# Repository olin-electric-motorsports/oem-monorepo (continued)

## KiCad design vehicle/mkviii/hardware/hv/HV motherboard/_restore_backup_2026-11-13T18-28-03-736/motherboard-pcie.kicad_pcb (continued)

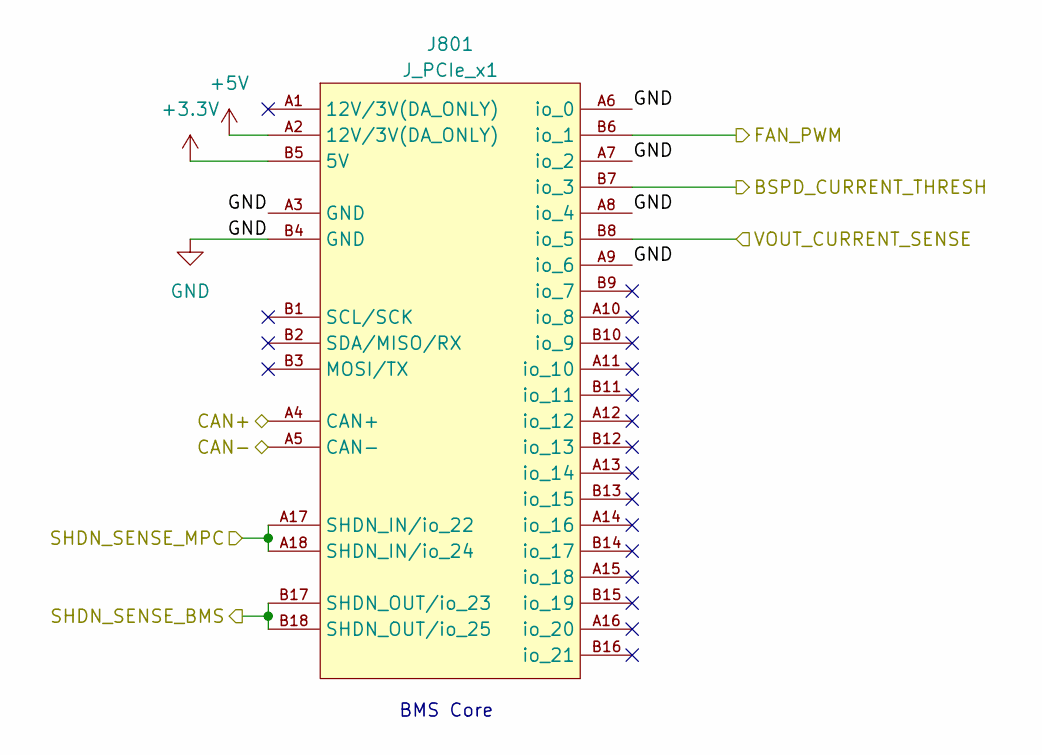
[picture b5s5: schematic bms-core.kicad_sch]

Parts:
J801: J_PCIe_x1; MPN 2-1761465-1

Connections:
+3.3V: J801.B5 (5V); also elsewhere on the board
+5V: J801.A2 (12V/3V(DA_ONLY)); also elsewhere on the board
/BSPD_CURRENT_THRESH: J801.B7 (io_3); also elsewhere on the board
/CAN+: J801.A4 (CAN+); also elsewhere on the board
/CAN-: J801.A5 (CAN-); also elsewhere on the board
/FAN_PWM: J801.B6 (io_1); also elsewhere on the board
/SHDN_SENSE_BMS: J801.B17 (SHDN_OUT/io_23), J801.B18 (SHDN_OUT/io_25); also elsewhere on the board
/SHDN_SENSE_MPC: J801.A17 (SHDN_IN/io_22), J801.A18 (SHDN_IN/io_24); also elsewhere on the board
/VOUT_CURRENT_SENSE: J801.B8 (io_5); also elsewhere on the board

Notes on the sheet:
BMS Core

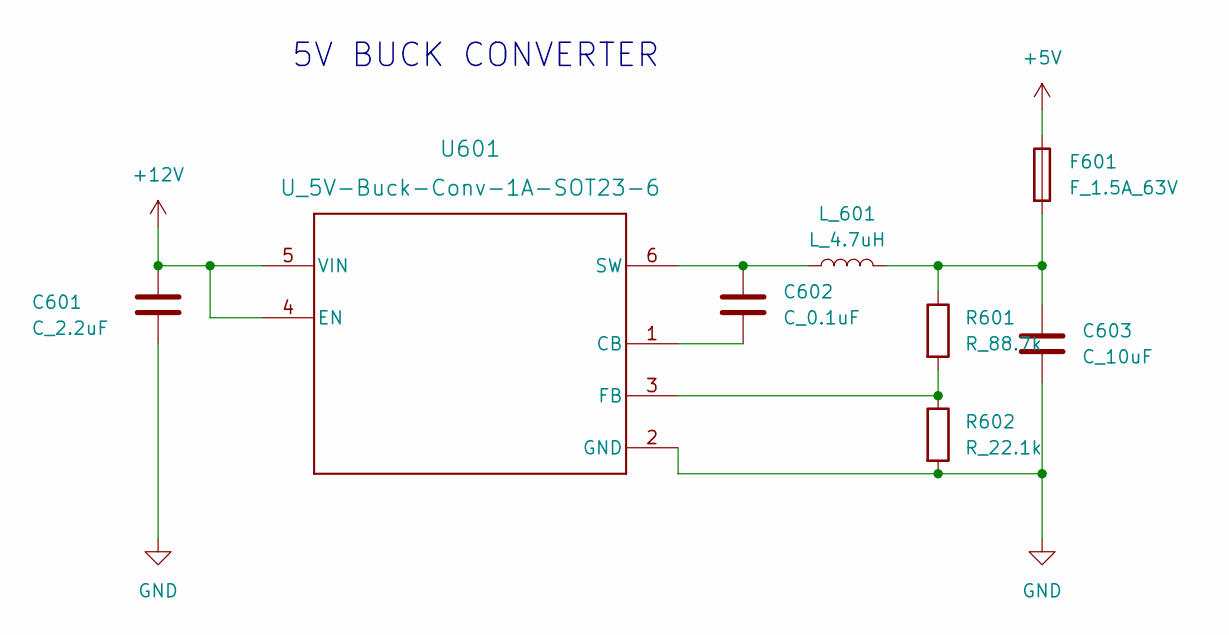
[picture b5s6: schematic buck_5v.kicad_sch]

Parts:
C601: C_2.2uF; C_0603_1608Metric; MPN GRM188R61E225KA12J
C602: C_0.1uF; C_0603_1608Metric; MPN C0603C104Z4VACTU
C603: C_10uF; C_0603_1608Metric; MPN GRM188D71A106KA73D
F601: F_1.5A_63V; Fuse_1206_3216Metric; MPN 046601.5NR
L_601: L_4.7uH; IND_ASPI-4030S-4R7M-T; MPN ASPI-4030S-4R7M-T
R601: R_88.7k; R_0603_1608Metric; MPN RMCF0603FT75K0
R602: R_22.1k; R_0603_1608Metric; MPN RMCF0603FT23K7
U601: U_5V-Buck-Conv-1A-SOT23-6; DBV0006A-IPC_A

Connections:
+5V: F601.1; also elsewhere on the board
unnamed: C603.1, F601.2, L_601.2, R601.1
unnamed: C602.2, U601.1 (CB)
unnamed: R601.2, R602.1, U601.3 (FB)
unnamed: C602.1, L_601.1, U601.6 (SW)

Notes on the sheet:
5V BUCK CONVERTER

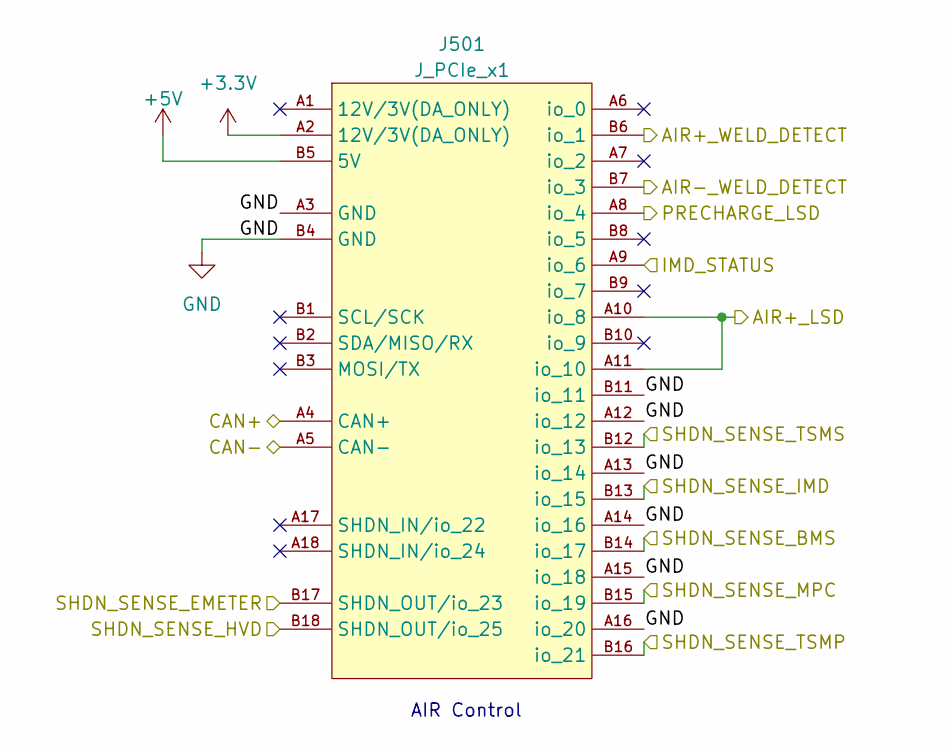
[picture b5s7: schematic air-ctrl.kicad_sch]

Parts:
J501: J_PCIe_x1; MPN 2-1761465-1

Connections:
+3.3V: J501.A2 (12V/3V(DA_ONLY)); also elsewhere on the board
+5V: J501.B5 (5V); also elsewhere on the board
/AIR+_LSD: J501.A10 (io_8), J501.A11 (io_10); also elsewhere on the board
/AIR+_WELD_DETECT: J501.B6 (io_1); also elsewhere on the board
/AIR-_WELD_DETECT: J501.B7 (io_3); also elsewhere on the board
/CAN+: J501.A4 (CAN+); also elsewhere on the board
/CAN-: J501.A5 (CAN-); also elsewhere on the board
/FINAL_SHDN: J501.B12 (io_13); also elsewhere on the board
/IMD_STATUS: J501.A9 (io_6); also elsewhere on the board
/PRECHARGE_LSD: J501.A8 (io_4); also elsewhere on the board
/SHDN_SENSE_BMS: J501.B14 (io_17); also elsewhere on the board
/SHDN_SENSE_EMETER: J501.B17 (SHDN_OUT/io_23); also elsewhere on the board
/SHDN_SENSE_HVD: J501.B18 (SHDN_OUT/io_25); also elsewhere on the board
/SHDN_SENSE_IMD: J501.B13 (io_15); also elsewhere on the board
/SHDN_SENSE_MPC: J501.B15 (io_19); also elsewhere on the board
/SHDN_SENSE_TSMP: J501.B16 (io_21); also elsewhere on the board

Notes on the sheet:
AIR Control

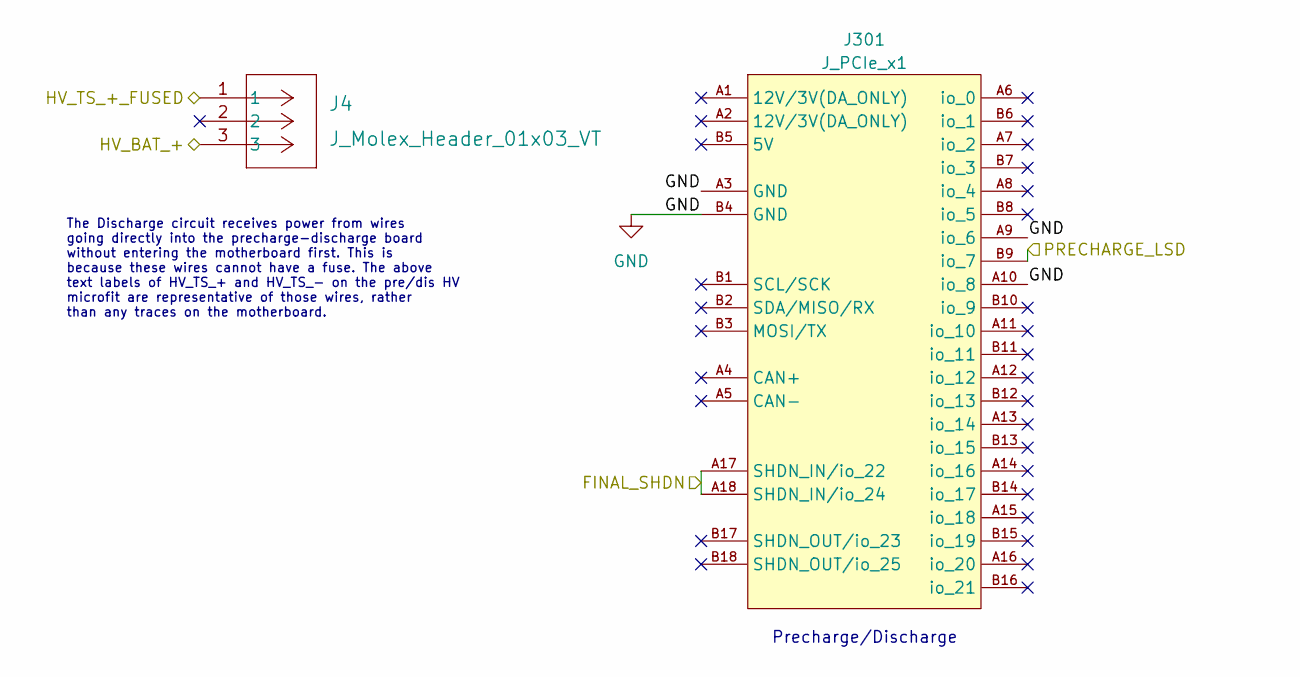
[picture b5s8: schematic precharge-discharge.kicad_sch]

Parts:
J4: J_Molex_Header_01x03_VT; J_Molex_Header_01x03_VT - 436500327
J301: J_PCIe_x1; MPN 2-1761465-1

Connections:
/FINAL_SHDN: J301.A17 (SHDN_IN/io_22), J301.A18 (SHDN_IN/io_24); also elsewhere on the board
/HV_BAT_+: J4.3; also elsewhere on the board
/HV_TS_+_FUSED: J4.1; also elsewhere on the board
/PRECHARGE_LSD: J301.B9 (io_7); also elsewhere on the board

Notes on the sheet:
Precharge/Discharge
The Discharge circuit receives power from wires going directly into the precharge-discharge board without entering the motherboard first. This is because these wires cannot have a fuse. The above text labels of HV_TS_+ and HV_TS_- on the pre/dis HV microfit are representative of those wires, rather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

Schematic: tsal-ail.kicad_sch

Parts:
J6: J_Molex_Header_01x03_VT; J_Molex_Header_01x03_VT - 436500327
J202: J_PCIe_x1; MPN 2-1761465-1
TP201: TP_SMD; TP_Hook_SMD; MPN 5019

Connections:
+5V: J202.B5 (5V); also elsewhere on the board
/HV_AIL_-: J6.1; also elsewhere on the board
/HV_TS_+_FUSED: J6.3; also elsewhere on the board
/RTM_LIGHT-: J202.A6 (io_0); also elsewhere on the board
/tsal-ail/RTM_LIGHT+: J202.A7 (io_2), TP201.1

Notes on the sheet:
Both Fused (1A) HV connections
Unused +12V output for RTM Light

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
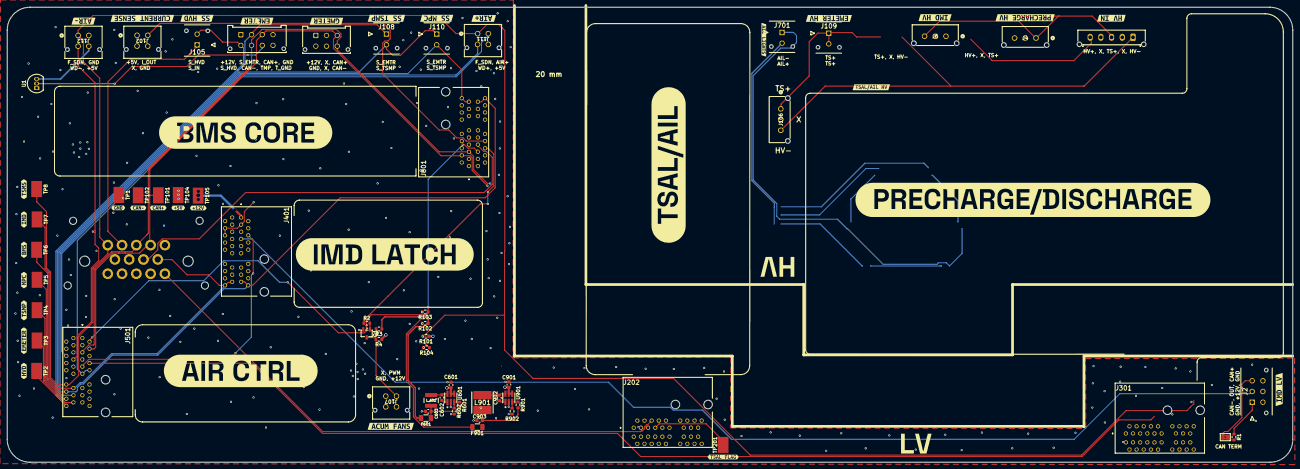
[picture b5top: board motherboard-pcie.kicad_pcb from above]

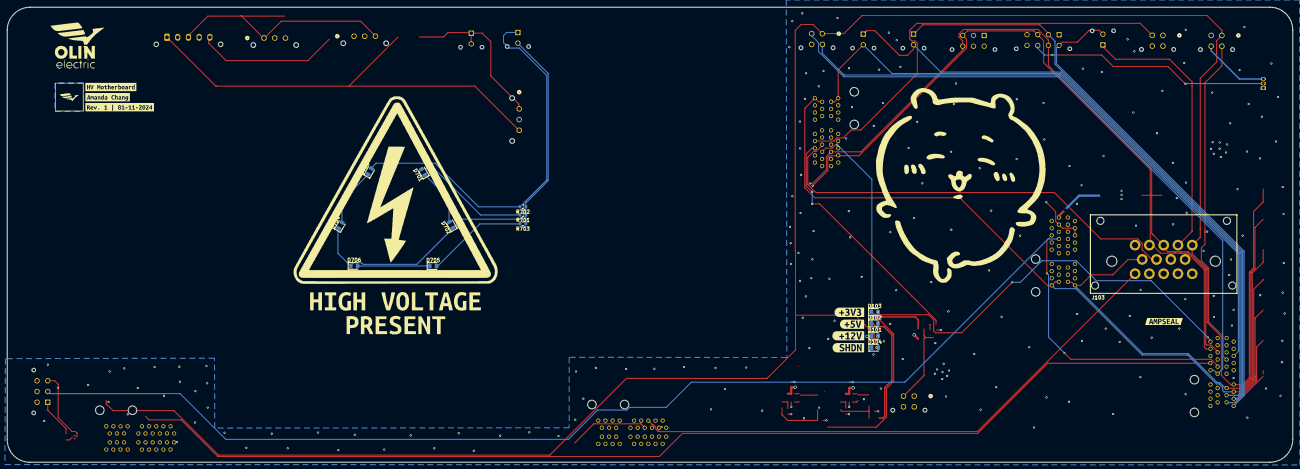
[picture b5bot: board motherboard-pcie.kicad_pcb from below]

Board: 4 copper layers, 359.7 x 127.3 mm, 121 parts (24 on the bottom side), 52 nets.

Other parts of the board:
kibuzzard-6AF3C239: G***; kibuzzard-6AF3C239
kibuzzard-6AF3C241: G***; kibuzzard-6AF3C241
kibuzzard-640B75B2: G***; kibuzzard-640B75B2
kibuzzard-640B76B0: G***; kibuzzard-640B76B0
kibuzzard-640B87CD: G***; kibuzzard-640B87CD
kibuzzard-640B861F: G***; kibuzzard-640B861F
kibuzzard-640B8645: G***; kibuzzard-640B8645
kibuzzard-640B8668: G***; kibuzzard-640B8668
kibuzzard-640B8680: G***; kibuzzard-640B8680
kibuzzard-677B3C3E: G***; kibuzzard-677B3C3E
kibuzzard-677B3C38: G***; kibuzzard-677B3C38
kibuzzard-677B3E90: G***; kibuzzard-677B3E90
kibuzzard-677CE749: G***; kibuzzard-677CE749
kibuzzard-677CFB84: G***; kibuzzard-677CFB84
kibuzzard-677CFB97: G***; kibuzzard-677CFB97
kibuzzard-677CFBA0: G***; kibuzzard-677CFBA0
kibuzzard-677E2BD4: G***; kibuzzard-677E2BD4
kibuzzard-677E2BDC: G***; kibuzzard-677E2BDC
kibuzzard-677E2BE2: G***; kibuzzard-677E2BE2
kibuzzard-677E2BE7: G***; kibuzzard-677E2BE7
kibuzzard-677E2BEC: G***; kibuzzard-677E2BEC
kibuzzard-677E2BF5: G***; kibuzzard-677E2BF5
kibuzzard-677E2BFE: G***; kibuzzard-677E2BFE
kibuzzard-677E26A9: G***; kibuzzard-677E26A9
kibuzzard-677E26B0: G***; kibuzzard-677E26B0
kibuzzard-677E26B5: G***; kibuzzard-677E26B5
kibuzzard-677E26BE: G***; kibuzzard-677E26BE
kibuzzard-677E26C5: G***; kibuzzard-677E26C5
kibuzzard-677E26CB: G***; kibuzzard-677E26CB
kibuzzard-677E26D4: G***; kibuzzard-677E26D4
kibuzzard-677E26ED: G***; kibuzzard-677E26ED
kibuzzard-677E335B: G***; kibuzzard-677E335B
kibuzzard-677E336E: G***; kibuzzard-677E336E
kibuzzard-677E3331: G***; kibuzzard-677E3331
kibuzzard-677E3355: G***; kibuzzard-677E3355
kibuzzard-677E3368: G***; kibuzzard-677E3368
kibuzzard-677FDCF4: G***; kibuzzard-677FDCF4
kibuzzard-6786FEE0: G***; kibuzzard-6786FEE0
kibuzzard-6786FEEF: G***; kibuzzard-6786FEEF
kibuzzard-678236F4: G***; kibuzzard-678236F4
kibuzzard-678238A8: G***; kibuzzard-678238A8
kibuzzard-678249D1: G***; kibuzzard-678249D1
kibuzzard-678771B8: G***; kibuzzard-678771B8
kibuzzard-67823702: G***; kibuzzard-67823702
kibuzzard-67823719: G***; kibuzzard-67823719
kibuzzard-67878439: G***; kibuzzard-67878439

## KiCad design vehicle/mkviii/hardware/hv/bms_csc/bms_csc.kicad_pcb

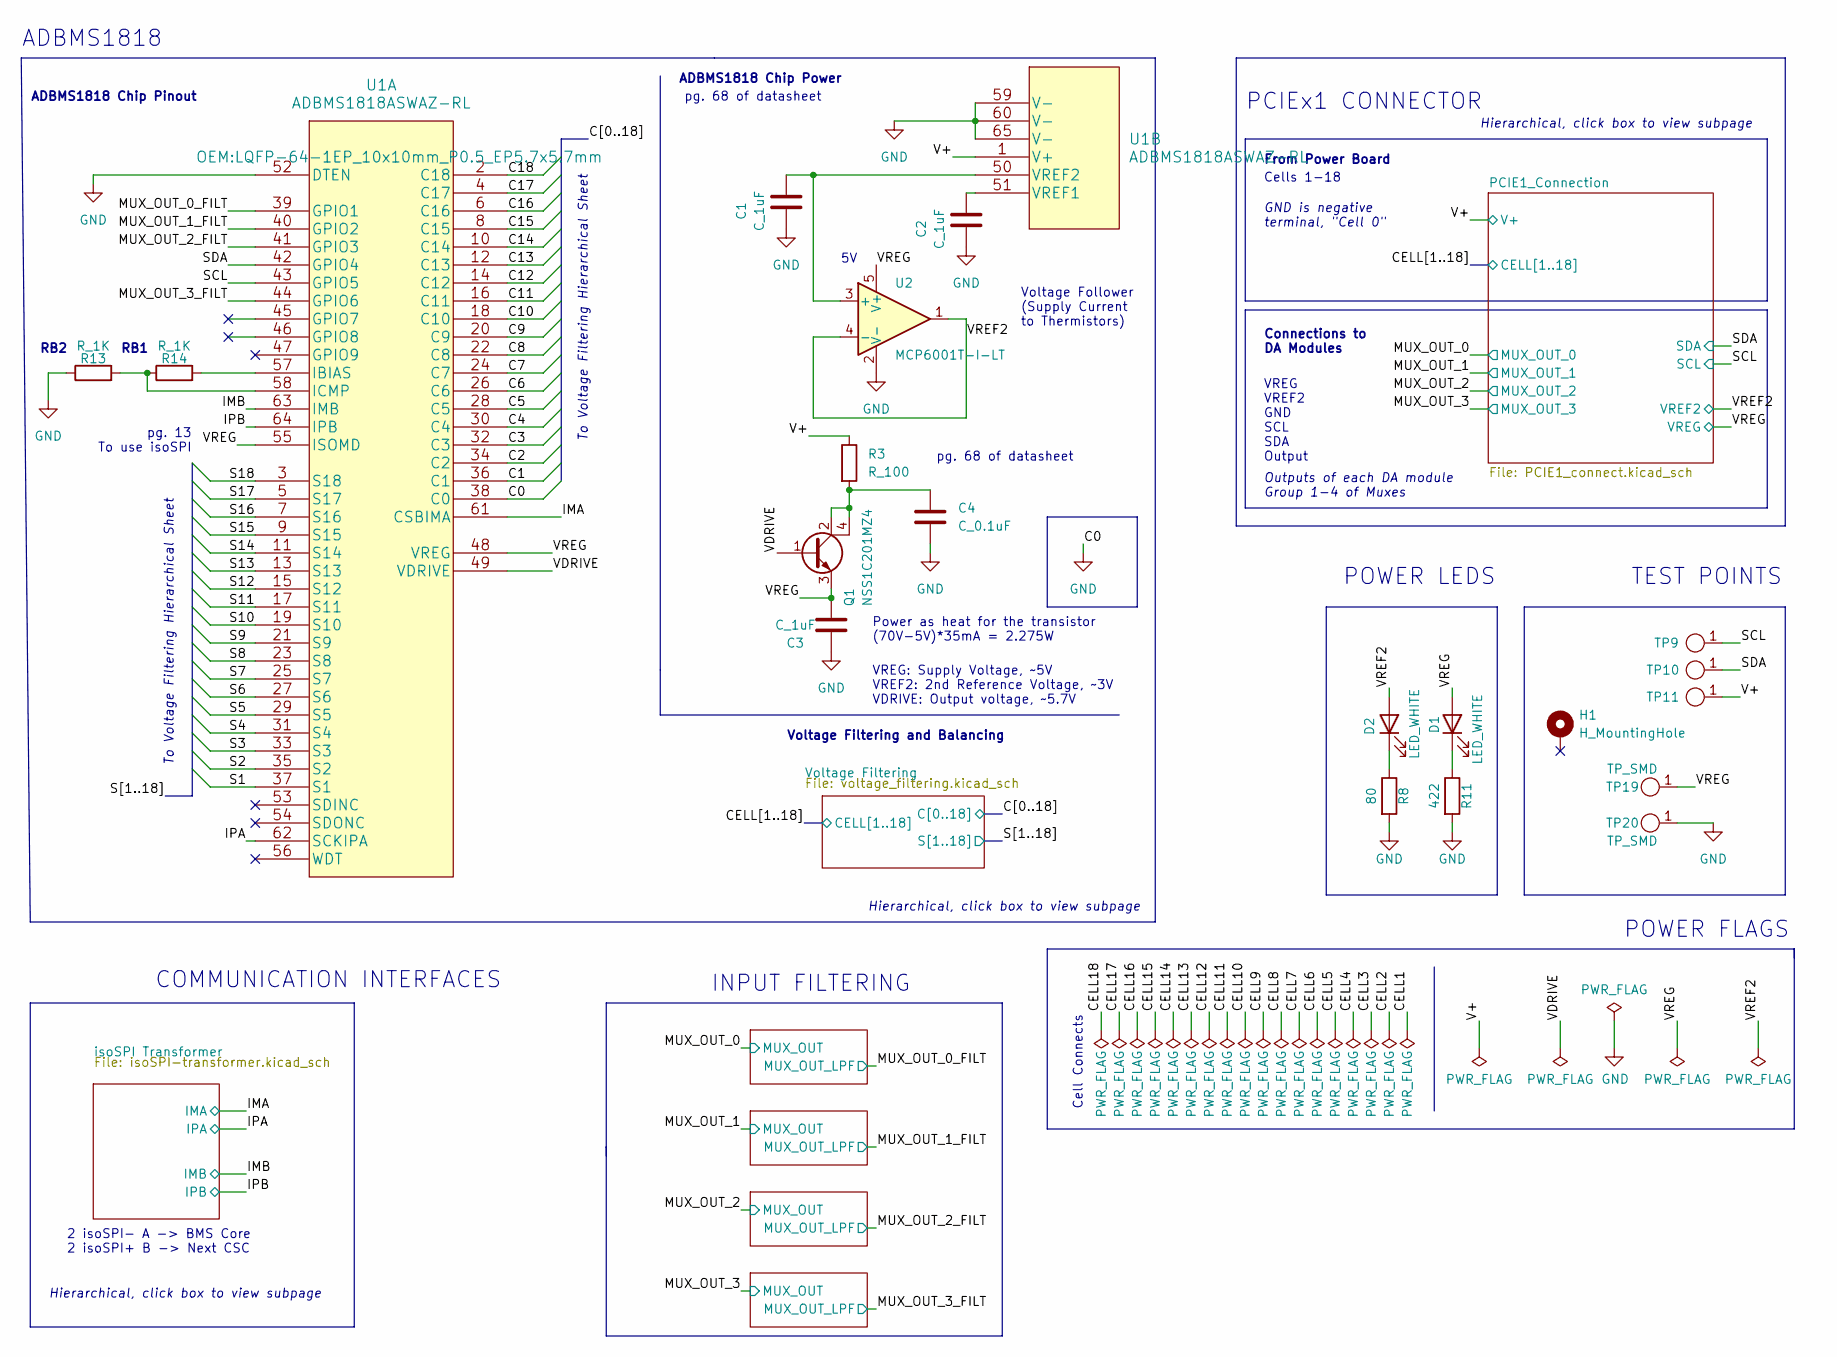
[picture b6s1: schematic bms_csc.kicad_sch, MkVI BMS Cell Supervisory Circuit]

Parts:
C1, C2, C3: C_1uF; C_0603; MPN CL10B105KA8NNNC
C4: C_0.1uF; C_0603; MPN CL10B104KB8NNWC
D1, D2: LED_WHITE; D_0805_2012Metric; MPN QBLP631-IW
H1: H_MountingHole
Q1: NSS1C201MZ4; SOT230P700X175-4N; MPN NSS1C201MZ4
R3: R_100; R_2512_6332Metric; MPN RMCF0603FT100R
R8: 80; R_0603; MPN RMCF0603FT1K00
R11: 422; R_0603; MPN RMCF0603FT1K00
R13, R14: R_1K; R_0603; MPN RMCF0603FT1K00
TP9, TP10, TP11: TP_1mm; Test_Point_SMD
TP19, TP20: TP_SMD; Test_Point_SMD; MPN 5019
U1: ADBMS1818ASWAZ-RL; LQFP-64-1EP_10x10mm_P0.5_EP5.7x5.7mm; MPN ADBMS1818ASWAZ-RL
U2: MCP6001T-I-LT; SOT-353_SC-70-5; MPN MCP6001T-I/OT

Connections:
/C1: U1.36 (C1); also elsewhere on the board
/C2: U1.34 (C2); also elsewhere on the board
/C3: U1.32 (C3); also elsewhere on the board
/C4: U1.30 (C4); also elsewhere on the board
/C5: U1.28 (C5); also elsewhere on the board
/C6: U1.26 (C6); also elsewhere on the board
/C7: U1.24 (C7); also elsewhere on the board
/C8: U1.22 (C8); also elsewhere on the board
/C9: U1.20 (C9); also elsewhere on the board
/C10: U1.18 (C10); also elsewhere on the board
/C11: U1.16 (C11); also elsewhere on the board
/C12: U1.14 (C12); also elsewhere on the board
/C13: U1.12 (C13); also elsewhere on the board
/C14: U1.10 (C14); also elsewhere on the board
/C15: U1.8 (C15); also elsewhere on the board
/C16: U1.6 (C16); also elsewhere on the board
/C17: U1.4 (C17); also elsewhere on the board
/C18: U1.2 (C18); also elsewhere on the board
/IMA: U1.61 (CSBIMA); also elsewhere on the board
/IMB: U1.63 (IMB); also elsewhere on the board
/IPA: U1.62 (SCKIPA); also elsewhere on the board
/IPB: U1.64 (IPB); also elsewhere on the board
/MUX_OUT_0_FILT: U1.39 (GPIO1); also elsewhere on the board
/MUX_OUT_1_FILT: U1.40 (GPIO2); also elsewhere on the board
/MUX_OUT_2_FILT: U1.41 (GPIO3); also elsewhere on the board
/MUX_OUT_3_FILT: U1.44 (GPIO6); also elsewhere on the board
/S1: U1.37 (S1); also elsewhere on the board
/S2: U1.35 (S2); also elsewhere on the board
/S3: U1.33 (S3); also elsewhere on the board
/S4: U1.31 (S4); also elsewhere on the board
/S5: U1.29 (S5); also elsewhere on the board
/S6: U1.27 (S6); also elsewhere on the board
/S7: U1.25 (S7); also elsewhere on the board
/S8: U1.23 (S8); also elsewhere on the board
/S9: U1.21 (S9); also elsewhere on the board
/S10: U1.19 (S10); also elsewhere on the board
/S11: U1.17 (S11); also elsewhere on the board
/S12: U1.15 (S12); also elsewhere on the board
/S13: U1.13 (S13); also elsewhere on the board
/S14: U1.11 (S14); also elsewhere on the board
/S15: U1.9 (S15); also elsewhere on the board
/S16: U1.7 (S16); also elsewhere on the board
/S17: U1.5 (S17); also elsewhere on the board
/S18: U1.3 (S18); also elsewhere on the board
/SCL: TP9.1, U1.43 (GPIO5); also elsewhere on the board
/SDA: TP10.1, U1.42 (GPIO4); also elsewhere on the board
/V+: R3.1, TP11.1, U1.1 (V+); also elsewhere on the board
/VDRIVE: Q1.1 (B), U1.49 (VDRIVE)
/VREF2: D2.2 (A), U2.1, U2.4 (-); also elsewhere on the board
/VREG: C3.2, D1.2 (A), Q1.3 (E), TP19.1, U1.48 (VREG), U1.55 (ISOMD), U2.5 (V+); also elsewhere on the board
unnamed: C4.1, Q1.2 (C), Q1.4 (C), R3.2
unnamed: D1.1 (K), R11.1
unnamed: D2.1 (K), R8.1
unnamed: R14.2, U1.57 (IBIAS)
unnamed: R13.2, R14.1, U1.58 (ICMP)
unnamed: C2.2, U1.51 (VREF1)
unnamed: C1.2, U1.50 (VREF2), U2.3 (+)

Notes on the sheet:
RB2
Hierarchical, click box to view subpage
INPUT FILTERING
From Power Board
Power as heat for the transistor (70V-5V)*35mA = 2.275W
pg. 68 of datasheet
Cells 1-18
ADBMS1818 Chip Pinout
Outputs of each DA module Group 1-4 of Muxes
2 isoSPI- A -> BMS Core 2 isoSPI+ B -> Next CSC
COMMUNICATION INTERFACES
pg. 13 To use isoSPI
Voltage Filtering and Balancing
Voltage Follower (Supply Current to Thermistors)
ADBMS1818 Chip Power
VREG VREF2 GND SCL SDA Output
VREG: Supply Voltage, ~5V VREF2: 2nd Reference Voltage, ~3V VDRIVE: Output voltage, ~5.7V
Connections to DA Modules
ADBMS1818
Cell Connects
POWER FLAGS
PCIEx1 CONNECTOR
RB1
POWER LEDS
GND is negative terminal, "Cell 0"
To Voltage Filtering Hierarchical Sheet
TEST POINTS

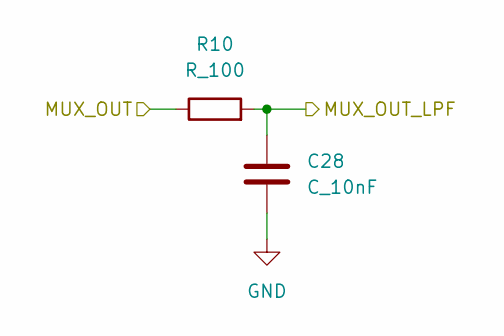
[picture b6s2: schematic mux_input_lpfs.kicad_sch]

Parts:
C28: C_10nF; C_0603; MPN CL10B104KB8NNWC
R10: R_100; R_0603; MPN RMCF0603FT100R

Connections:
/MUX_OUT_1: R10.1; also elsewhere on the board
/MUX_OUT_1_FILT: C28.1, R10.2; also elsewhere on the board

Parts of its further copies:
C27, C29, C30: C_10nF; C_0603; MPN CL10B104KB8NNWC
R9, R12, R51: R_100; R_0603; MPN RMCF0603FT100R

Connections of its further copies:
/MUX_OUT_0: R9.1; also elsewhere on the board
/MUX_OUT_0_FILT: C27.1, R9.2; also elsewhere on the board
/MUX_OUT_2: R12.1; also elsewhere on the board
/MUX_OUT_2_FILT: C29.1, R12.2; also elsewhere on the board
/MUX_OUT_3: R51.1; also elsewhere on the board
/MUX_OUT_3_FILT: C30.1, R51.2; also elsewhere on the board

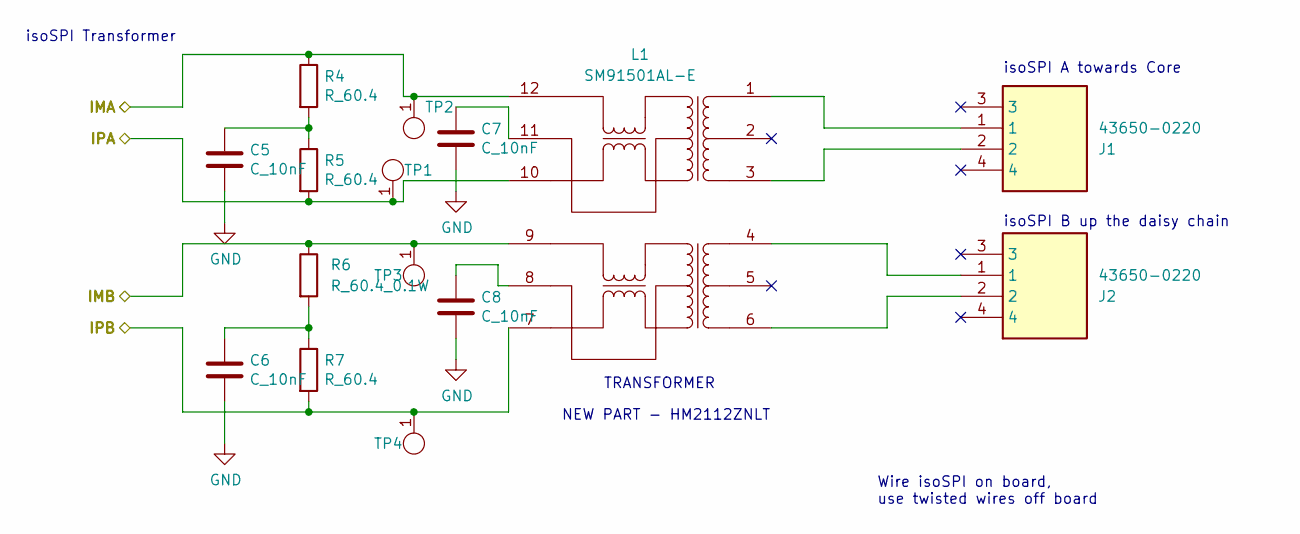
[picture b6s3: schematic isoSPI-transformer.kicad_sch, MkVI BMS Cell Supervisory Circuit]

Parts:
C5, C6, C7, C8: C_10nF; C_0603; MPN CL10B103KB8NNNC
J1, J2: 43650-0220; 43650-02YY_18192063; Manufacturer_Part_Number 43650-0220; Mouser Part Number 538-43650-0220
L1: SM91501AL-E; SOP200P1473X500-12N (L_BMS-isoSPI-Transformer_SM91501AL-E_S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; MPN SM91501AL-E
R4, R5, R7: R_60.4; R_0603; MPN RMCF0603FT60R4
R6: R_60.4_0.1W; R_0603_1608Metric; MPN RMCF0603FT60R4
TP1, TP2, TP3, TP4: TP_SMD; Test_Point_SMD; MPN 5019

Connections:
/IMA: L1.12, R4.1, TP2.1; also elsewhere on the board
/IMB: L1.9, R6.1, TP3.1; also elsewhere on the board
/IPA: L1.10, R5.2, TP1.1; also elsewhere on the board
/IPB: L1.7, R7.2, TP4.1; also elsewhere on the board
unnamed: C5.1, R4.2, R5.1
unnamed: C6.1, R6.2, R7.1
unnamed: C7.1, L1.11
unnamed: C8.1, L1.8
unnamed: J1.1, L1.1
unnamed: J1.2, L1.3
unnamed: J2.1, L1.4
unnamed: J2.2, L1.6

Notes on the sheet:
isoSPI B up the daisy chain
TRANSFORMER
isoSPI Transformer
NEW PART - HM2112ZNLT
isoSPI A towards Core
Wire isoSPI on board, use twisted wires off board

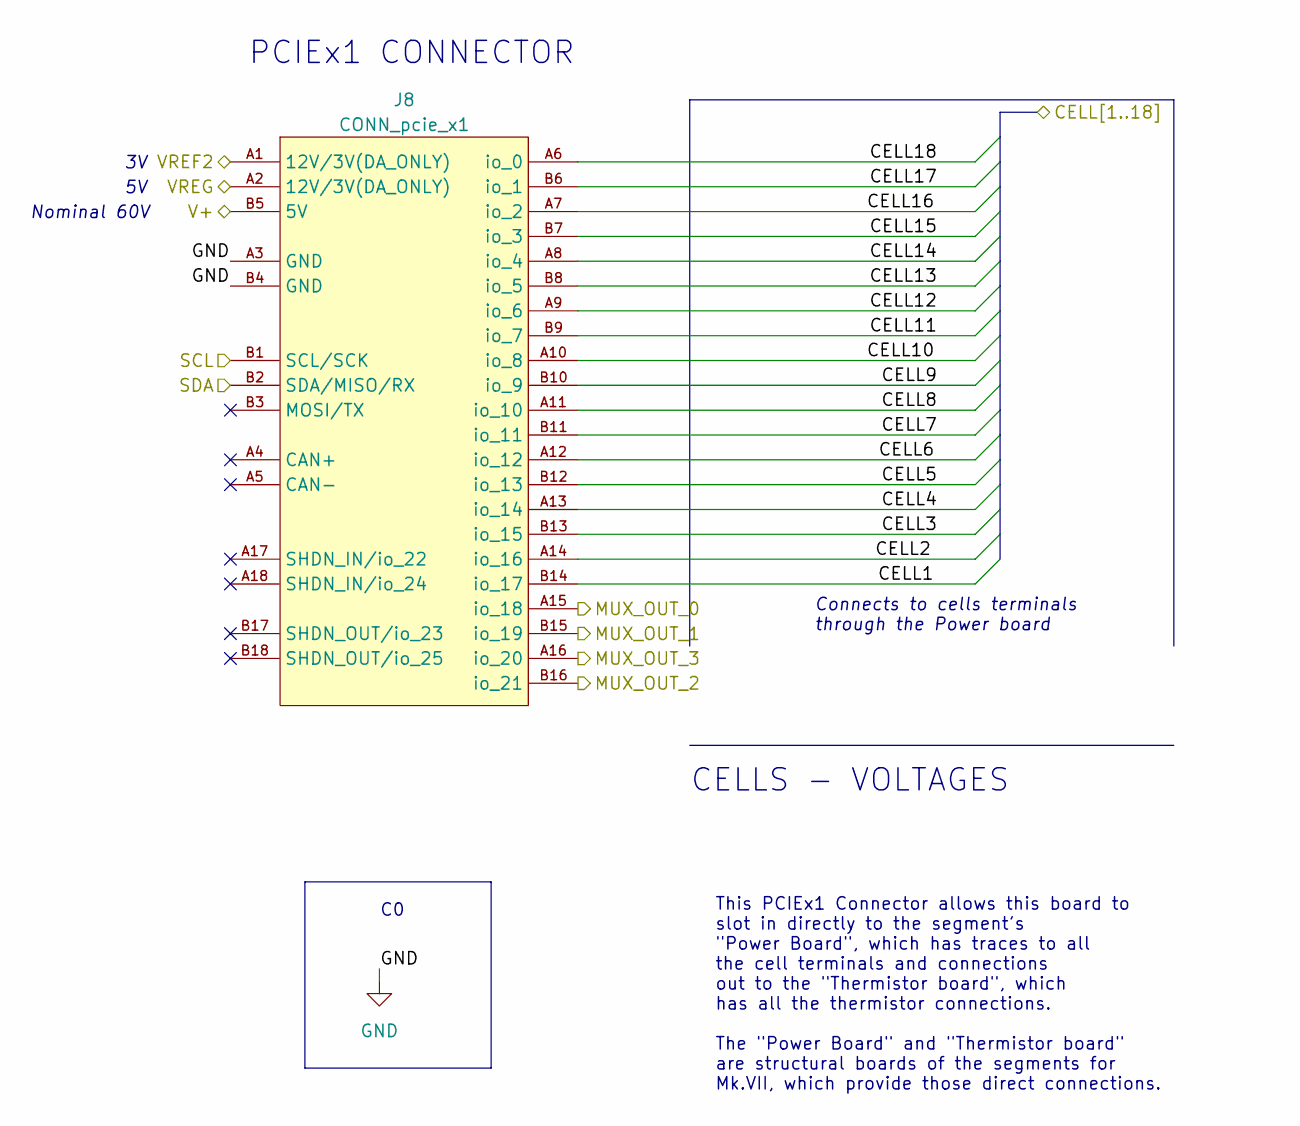
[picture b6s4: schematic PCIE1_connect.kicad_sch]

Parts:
J8: CONN_pcie_x1; pcie_x1

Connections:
/CELL1: J8.B14 (io_17); also elsewhere on the board
/CELL2: J8.A14 (io_16); also elsewhere on the board
/CELL3: J8.B13 (io_15); also elsewhere on the board
/CELL4: J8.A13 (io_14); also elsewhere on the board
/CELL5: J8.B12 (io_13); also elsewhere on the board
/CELL6: J8.A12 (io_12); also elsewhere on the board
/CELL7: J8.B11 (io_11); also elsewhere on the board
/CELL8: J8.A11 (io_10); also elsewhere on the board
/CELL9: J8.B10 (io_9); also elsewhere on the board
/CELL10: J8.A10 (io_8); also elsewhere on the board
/CELL11: J8.B9 (io_7); also elsewhere on the board
/CELL12: J8.A9 (io_6); also elsewhere on the board
/CELL13: J8.B8 (io_5); also elsewhere on the board
/CELL14: J8.A8 (io_4); also elsewhere on the board
/CELL15: J8.B7 (io_3); also elsewhere on the board
/CELL16: J8.A7 (io_2); also elsewhere on the board
/CELL17: J8.B6 (io_1); also elsewhere on the board
/CELL18: J8.A6 (io_0); also elsewhere on the board
/MUX_OUT_0: J8.A15 (io_18); also elsewhere on the board
/MUX_OUT_1: J8.B15 (io_19); also elsewhere on the board
/MUX_OUT_2: J8.B16 (io_21); also elsewhere on the board
/MUX_OUT_3: J8.A16 (io_20); also elsewhere on the board
/SCL: J8.B1 (SCL/SCK); also elsewhere on the board
/SDA: J8.B2 (SDA/MISO/RX); also elsewhere on the board
/V+: J8.B5 (5V); also elsewhere on the board
/VREF2: J8.A1 (12V/3V(DA_ONLY)); also elsewhere on the board
/VREG: J8.A2 (12V/3V(DA_ONLY)); also elsewhere on the board

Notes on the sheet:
This PCIEx1 Connector allows this board to slot in directly to the segment's "Power Board", which has traces to all the cell terminals and connections out to the "Thermistor board", which has all the thermistor connections. The "Power Board" and "Thermistor board" are structural boards of the segme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
CELLS - VOLTAGES
PCIEx1 CONNECTOR
Connects to cells terminals through the Power board
Nominal 60V

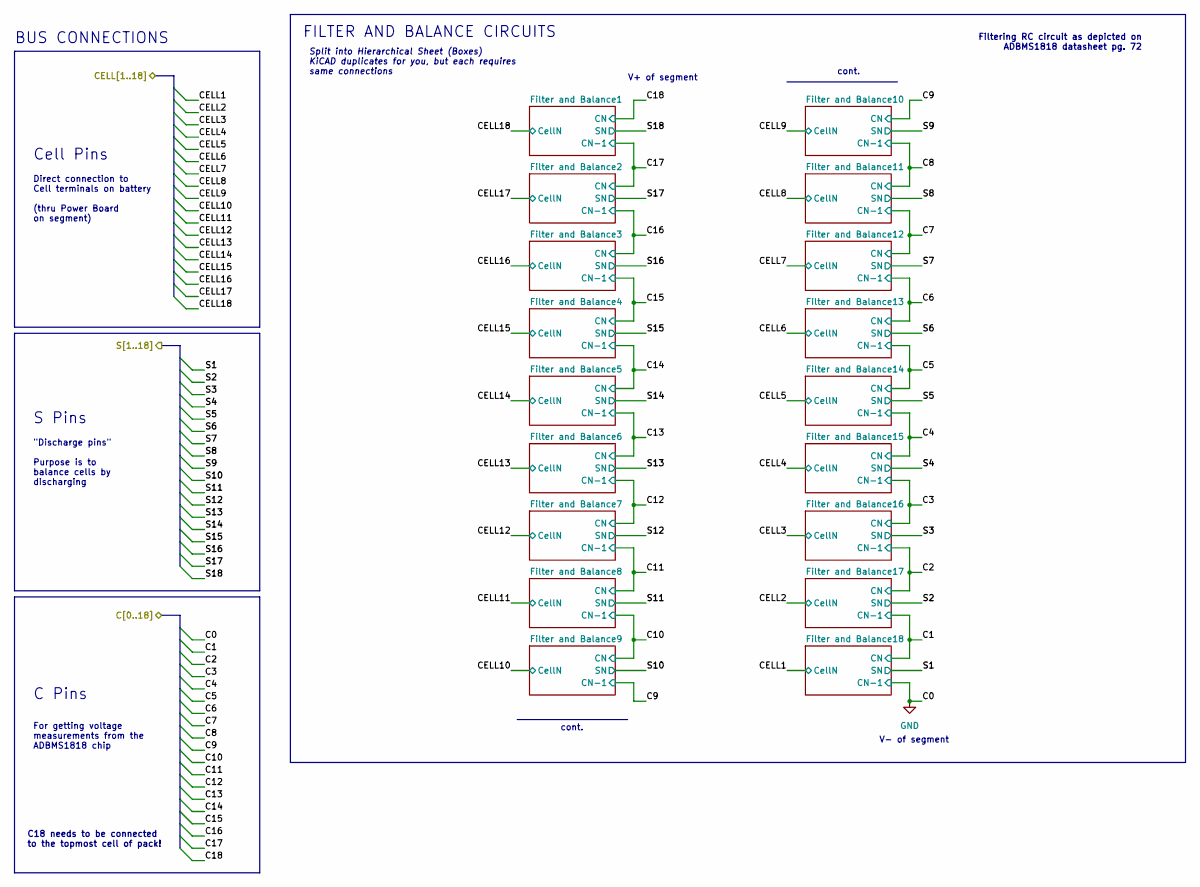
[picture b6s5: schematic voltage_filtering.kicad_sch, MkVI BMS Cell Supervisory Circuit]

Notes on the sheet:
BUS CONNECTIONS
C18 needs to be connected to the topmost cell of pack!
For getting voltage measurements from the ADBMS1818 chip
cont.
Cell Pins
Direct connection to Cell terminals on battery (thru Power Board on segment)
C Pins
V+ of segment
Filtering RC circuit as depicted on ADBMS1818 datasheet pg. 72
V- of segment
FILTER AND BALANCE CIRCUITS
S Pins
"Discharge pins" Purpose is to balance cells by discharging
Split into Hierarchical Sheet (Boxes) KiCAD duplicates for you, but each requires same connections
